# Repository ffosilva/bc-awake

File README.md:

# BC Awake

### ESP32-based smart ATX PSU switch for AMD BC250 with Bluetooth & Wake-on-LAN

The AMD **BC250** is a powerhouse for budget desktop conversions, living room gaming, and local AI workloads — but because it was designed for mining, it lacks an ATX power button and has **no low-power sleep states**, wasting power and generating heat if left idling 24/7.

**BC Awake** solves this by turning an ESP32 into an intelligent power controller for your ATX/SFX PSU (`PS_ON#`). Instead of leaving the system running or fiddling with power cables, BC Awake keeps the machine completely off and brings it up on demand:

- 🎮 **Living Room Console**: Pick up your Bluetooth gamepad (PS4/PS5, Xbox, Switch Pro, 8BitDo) and press the home button — the PC powers on right from your couch.
- ⚡ **On-Demand AI & Game Streaming**: Wake the machine over Wi-Fi via Wake-on-LAN when connecting through Moonlight, Steam Link, or launching intermittent AI model inference and processing workflows.
- 🔘 **Complete Power Management**: Provides a physical power button, automatic PSU shutoff when the OS halts, optional graceful ACPI shutdown, boot watchdog protection, and a captive Wi-Fi portal with OTA firmware updates.

Supports multiple targets from the same repository:
- **ESP32-WROOM (DevKitC)**: Classic Bluetooth (BR/EDR) controller wake.
- **AI-Thinker ESP32-CAM (Bare module)**: Classic Bluetooth wake with onboard flash LED wake indicator.
- **AI-Thinker ESP32-CAM (Carrier Board)**: Dedicated carrier target with BC547/BC548 transistor buffer and ADC2 sensing.
- **ESP32-C3 (SuperMini / DevKitM-1)**: Bluetooth Low Energy (BLE) controller wake.

> [!CAUTION]
> **Hardware Disclaimer**: This project involves custom wiring, ATX power line manipulation, and bare-board hardware. The author is **not responsible** for any BC-250 damages, dead cards, fried components, or any kind of losses or damages resulting from using this firmware, schematics, or documentation. Proceed at your own risk! If deploying the AI-Thinker ESP32-CAM, review the [hardware resilience circuit](docs/pinout.md#ai-thinker-esp32-cam-hardware-resilience-circuit-anti-oscillation) to prevent brownout reboot loops.

## Features

- **Push-button power**: tap to turn on; hold 5 s while running to force off.
- **Follows the board**: if the OS shuts the board down, the PSU is cut automatically.
- **Graceful shutdown** (optional): wire the motherboard's `PWR_BTN#` header to the ESP32 and the button (and a portal "Shut down" action) acts like the real power button — see [Graceful shutdown](#graceful-shutdown-optional).
- **Boot watchdog**: if the board doesn't come up within 10 s, the PSU is released.
- **Bluetooth controller wake** (optional):
  - **Classic Bluetooth (BR/EDR)** on ESP32 / ESP32-CAM (PS4/PS5, Xbox, Switch Pro, 8BitDo in Classic mode).
  - **BLE advertisement wake** on ESP32-C3 (controllers operating in BLE mode).
- **Wake-on-LAN (WOL) over Wi-Fi** (optional): wake the BC250 from Moonlight, Steam Link, or mobile WOL apps targeting your PC's Ethernet MAC address.
- **WiFi setup portal**: configure bound controllers and Wake-on-LAN settings from a phone — no reflashing.
- **Over-the-Air (OTA) firmware updates**: update firmware wirelessly via the setup portal web UI.
- **Firmware versioning**: compile-time semantic versioning and target hardware reporting.

## Wiring

The ESP32 is permanently powered from the ATX connector's **5 V standby** (into the
`5V` / VIN pin), so it runs whether the machine is on or off. Share a common ground
between the ESP, the PSU, and the board.

| ESP32 (DevKitC) | ESP32-CAM | ESP32-C3 | Connects to | Notes |
|-----------------|-----------|----------|-------------|-------|
| GPIO25 | GPIO15 | GPIO5 | Momentary switch, terminal A | Read with internal pull-up |
| GPIO26 | GND (header) | GPIO6 | Momentary switch, terminal B | DevKitC/C3 drives LOW; CAM wires directly to GND |
| GPIO32 | GPIO14 | GPIO4 | ATX `PS_ON#` (green wire) | **Open-drain**, active LOW: LOW = PSU on, released = off |
| GPIO34 | GPIO13 | GPIO3 | BC250 `TPMS1` (pin 9) | ~3.3 V when the board is up, 0 when off (ADC voltage) |
| GPIO27 | GPIO2 | GPIO7 | Motherboard `PWR_BTN#` (optional) | Direct wire; high-Z input, pulled LOW only to emulate a press. See [Graceful shutdown](#graceful-shutdown-optional) |
| 5V / GND | 5V / GND | 5V / GND | PSU standby + common ground | Permanent power for the ESP |

> **`PS_ON#` is 5 V.** It idles at ~5 V (pulled up inside the PSU), above the ESP32's
> GPIO maximum (~3.6 V). Open-drain keeps the ESP from *driving* 5 V, but the pin still
> sees it. A small N-MOSFET/NPN buffer (or at least a ~1 kΩ series resistor) is
> **recommended** — see [docs/pinout.md](docs/pinout.md#ps_on-5-v-caution-recommended-buffer).

`TPMS1` is a higher-impedance signal that hovers near the logic threshold, so it's read
as an analog voltage with hysteresis rather than a digital pin (ADC1 on DevKitC and ESP32-C3; digital input with pull-down on ESP32-CAM).

> [!TIP]
> **ESP32-CAM deployments**: Due to the onboard AMS1117-3.3 regulator's dropout voltage and the 47 kΩ MicroSD pull-up on GPIO13, ESP32-CAM builds are prone to brownout resets and threshold floating. Adding power bulk decoupling (470 µF), an external 4.7 kΩ pull-down on GPIO13, and a BC547/BC548 NPN buffer on GPIO14 is strongly recommended for 24/7 reliability. When using this circuit or the carrier board, flash with `pio run -e esp32cam-carrier -t upload`. See [docs/pinout.md: ESP32-CAM resilience circuit](docs/pinout.md#ai-thinker-esp32-cam-hardware-resilience-circuit-anti-oscillation), the [carrier board guide](docs/esp32cam-carrier-pcb.md), and the dedicated [Bill of Materials](docs/bom.md).

**Full pinout, header diagrams for DevKitC, ESP32-CAM, and ESP32-C3 (SuperMini & DevKitM-1), ATX 24-pin and TPMS1 connector diagrams, the
`PS_ON#` buffer circuit, and the ESP32-CAM resilience circuit: [docs/pinout.md](docs/pinout.md).**

## Button controls

| Action | Result |
|--------|--------|
| Tap while **off** | Power on |
| Hold ≥ 5 s while **on** | Force power off |
| Hold ≥ 8 s while **off** | Enter WiFi setup portal |

The button is the primary control and always works, even with no controller configured.

## Graceful shutdown (optional)

By default the only way the ESP can turn the board off is to cut the PSU (`PS_ON#`), which
is a hard power-off. If you also wire the motherboard's front-panel **`PWR_BTN#`** pin to the
ESP32 (GPIO27 on DevKitC, GPIO2 on ESP32-CAM, GPIO7 on ESP32-C3) and enable the feature in the portal's **Power** tab, the ESP behaves like a real power button:

| Action (feature enabled, machine **on**) | Result |
|------------------------------------------|--------|
| Short press | Mirrored to the board: OS gets an ACPI power-button event and shuts down cleanly |
| Hold the button | Mirrored to the board for as long as you hold it, so the board's own long-press override can apply |
| Hold ≥ 5 s | Unchanged backstop: the PSU is cut immediately |

When the board powers down, `TPMS1` goes low and the existing logic releases `PS_ON#`
automatically. There is no timeout: if the OS hangs, you decide (hold the button 5 s to cut
power). Presses made while the machine is off or booting behave exactly as before. The
`PWR_BTN#` line idles at ~3.4 V on the BC250 board, so it is wired directly and the ESP32
never drives it high. Wiring details: [docs/pinout.md](docs/pinout.md).

## Bluetooth controller wake

This uses **classic Bluetooth (BR/EDR)**, the kind used by most gamepads when paired to
a PC (DualShock 4 / DualSense, Xbox Wireless, 8BitDo, Nintendo Switch Pro Controller / Joy-Con).

A powered-on, paired classic controller doesn't advertise; it *pages* its bonded host.
While the machine is **off**, the ESP32 takes on the BC250's Bluetooth adapter address
and runs **continuous, interlaced page listening**:

1. You turn on the controller (e.g. press the **HOME button** on a Switch controller, or
   power button on an 8BitDo/Xbox/PS controller) → the controller pages its host.
2. The ESP32 catches the page and **rejects** the connection (no link, no authentication,
   so the controller's pairing with the BC250 is never touched) but counts it as
   "controller present", and powers the machine on.
3. Once the machine is powering on, the ESP32 goes silent (stops answering pages). The
   controller's next attempt reaches the real BC250 adapter and connects normally.

When controllers are bound (via the portal), the machine **follows any of your bound controllers**:
turn on any bound controller (up to 8 supported simultaneously) and the machine powers up.
After a power-off there's a short guard window so the controller's reconnect burst can't immediately
switch it back on — turn the controller off within that window to keep the machine down.

Requirements:

- The controller must already be **paired to the BC250**.
- You must give the ESP32 the BC250 Bluetooth **adapter MAC**: on Linux run
  `bluetoothctl show` (the `Controller aa:bb:cc:dd:ee:ff` line); on Windows, Device
  Manager → Bluetooth adapter → Properties → Advanced.

## Wake-on-LAN (Network Wake)

The BC250's onboard Ethernet controller is unpowered when the SFX PSU is off, so it cannot
receive Wake-on-LAN packets natively. When **Enable Wake-on-LAN** is configured:

1. The ESP32 connects to your Wi-Fi network in station (STA) mode and listens for standard
   WOL Magic Packets on UDP ports 9 and 7.
2. When a Magic Packet matching your configured **BC250 Ethernet MAC** arrives from a
   streaming app (Moonlight, Steam Link) or LAN tool, the ESP32 asserts `PS_ON#` to boot the PC.
3. Supports both password-protected and open (passwordless) networks.
4. If disabled, the Wi-Fi radio stays completely off in normal mode for zero RF/power overhead.

## Setup portal

When unconfigured (or after a factory reset), the ESP32 **automatically launches the setup portal** (`BC250_<SUFFIX>`) on initial power-up. While in setup mode, the host machine remains safely powered off and unenergized so you can configure the switch from your smartphone, tablet, or laptop.

If the switch is already configured, hold the power button ≥ 8 s while OFF (or send `'s'` over serial while off) to re-enter setup mode. Hold ≥ 8 s again while in setup mode to return to normal operation.

On every ESP32-CAM build (with or without the carrier board) the onboard red LED (GPIO33) shows the state: off = machine off, fast blink = booting, solid = machine on, 1 Hz blink = setup mode.

### Setup Instructions

1. Connect your smartphone, tablet, or laptop to the open Wi-Fi network **`BC250_<SUFFIX>`** and open `http://192.168.4.1`.
2. Create a portal password (min 6 characters).
3. Access the tabbed interface:
   - **Bluetooth tab**:
     - Enter and save your BC250 Bluetooth adapter MAC (run `bluetoothctl show` on Linux to copy it).
     - Manage controllers: bind paired controllers interactively or add MACs manually (up to 8 controllers).
     - (ESP32-CAM) Toggle flash LED blink on wake.
   - **Network tab**:
     - Configure Wake-on-LAN: check **Enable Wake-on-LAN (Wi-Fi)**, enter your home Wi-Fi SSID, password, device hostname, and BC250 Ethernet MAC address (from `ip link`), then click **Save Network Settings**.
   - **Power tab**:
     - Motherboard power button: toggle optional `PWR_BTN#` mirroring for clean OS shutdown on short press.
   - **System tab**:
     - Firmware update (OTA): upload a compiled `.bin` binary wirelessly.
     - Change portal password or reset configuration back to defaults.
     - Click **Exit setup mode & reboot** to restart the switch into normal operation.

## Build & flash

PlatformIO (pioarduino). Flashing is a single step — the setup portal web UI (`app/index.html`) is automatically gzipped and embedded directly into the firmware binary during the build.

**ESP32-DevKitC (`esp32dev`, default — Classic BT wake):**
```bash
pio run -e esp32dev -t upload
```

**AI-Thinker ESP32-CAM (Bare module — Classic BT wake):**
```bash
pio run -e esp32cam -t upload
```
> *ESP32-CAM flashing note*: Use a USB-to-UART adapter (or ESP32-CAM-MB base board). Connect **GPIO0 to GND** before powering on to enter download mode; disconnect GPIO0 and reset to run.

**AI-Thinker ESP32-CAM (Carrier Board with BC547/BC548 buffer):**
```bash
pio run -e esp32cam-carrier -t upload
```

**ESP32-C3 DevKitM-1 (`esp32-c3-devkitm-1` — BLE wake):**
```bash
pio run -e esp32-c3-devkitm-1 -t upload
```

### Over-the-Air (OTA) Updates

Once the device has been flashed with the dual-bank partition table via USB, all future updates can be applied wirelessly:

1. Compile the firmware binary for your target:
   ```bash
   pio run -e esp32dev   # binary generated at .pio/build/esp32dev/firmware.bin
   ```
2. Hold the switch button ≥ 8 s while OFF to enter the setup portal.
3. Connect to **`BC Awake Setup`** (`http://192.168.4.1`) and unlock.
4. In the **Firmware update (OTA)** card, select your `.bin` file and click **Upload & flash**.
5. The device flashes the inactive bank and automatically reboots into the updated firmware.

> **Note on Initial Partitioning**: The switch uses a dual-bank 1.81 MB OTA layout (`partitions.csv`). Transitioning from older single-partition builds requires **one initial wired flash** (`pio run -t upload`) to repartition flash.

## Notes

- **Multi-target support**: Switching between Classic Bluetooth (ESP32 / ESP32-CAM) and BLE (ESP32-C3) is done by choosing the PlatformIO environment target (`-e esp32dev`, `-e esp32cam`, or `-e esp32-c3-devkitm-1`).
- **WiFi TX power** for the portal's SoftAP is `AP_TX_POWER` in
  [include/board.h](include/board.h) (lowered automatically on ESP32-C3 to prevent the mini RF bug).
- Serial debug runs at **115200** baud.
- Pin assignments and all timing constants live in [include/board.h](include/board.h).

## How to Contribute

Contributions are what make open-source projects thrive! Whether you are an experienced embedded developer or just getting started with ESP32s, your help is welcome and deeply appreciated. Every contribution — from reporting a minor bug to adding support for new hardware — helps make BC Awake better for everyone.

### Ways you can help

- **Report bugs and issues**: Encountered unexpected behavior, boot watchdog resets, or connection issues? [Open an issue](https://github.com/ffosilva/bc-awake/issues) detailing your hardware board, controller model, and serial logs (`115200` baud).
- **Suggest features & improvements**: Have ideas for additional controller modes, new hardware targets, or web portal enhancements? Open a feature request to start a discussion.
- **Submit Pull Requests**: Bug fixes, code optimizations, web UI updates, and documentation improvements are all welcome.
- **Test hardware & controllers**: BC Awake supports various ESP32 boards (DevKitC, ESP32-CAM, ESP32-C3) and countless Bluetooth/BLE controllers. Testing on your hardware and reporting what works helps expand our compatibility list.

### Architectural Decisions & OpenSpec

This project uses [OpenSpec](openspec/) to track architectural decisions, system specifications, and planned changes under the `openspec/` directory.

- **Great to have**: If you're planning a larger architectural change or new subsystem, proposing or documenting it via OpenSpec is a fantastic bonus and helps maintain a clear history of design choices.
- **Not a requirement**: You do **not** need to learn or use OpenSpec to contribute. Feel free to open a regular issue or pull request, and we will happily collaborate with you to help integrate your changes and document any specs needed.

### Getting Started with PRs

1. Fork the repository and clone your fork locally.
2. Create a feature branch (`git checkout -b feature/my-feature`).
3. Make your changes and test the build for relevant targets (e.g., `pio run -e esp32dev`).
4. Commit your changes using clear commit messages.
5. Push to your branch and open a Pull Request with a summary of what you did and why.

## Support

If you find BC Awake useful and would like to support its ongoing development, consider buying me a coffee:

## License

This project is licensed under the GNU General Public License v3.0 - see the [LICENSE](LICENSE) file for details.

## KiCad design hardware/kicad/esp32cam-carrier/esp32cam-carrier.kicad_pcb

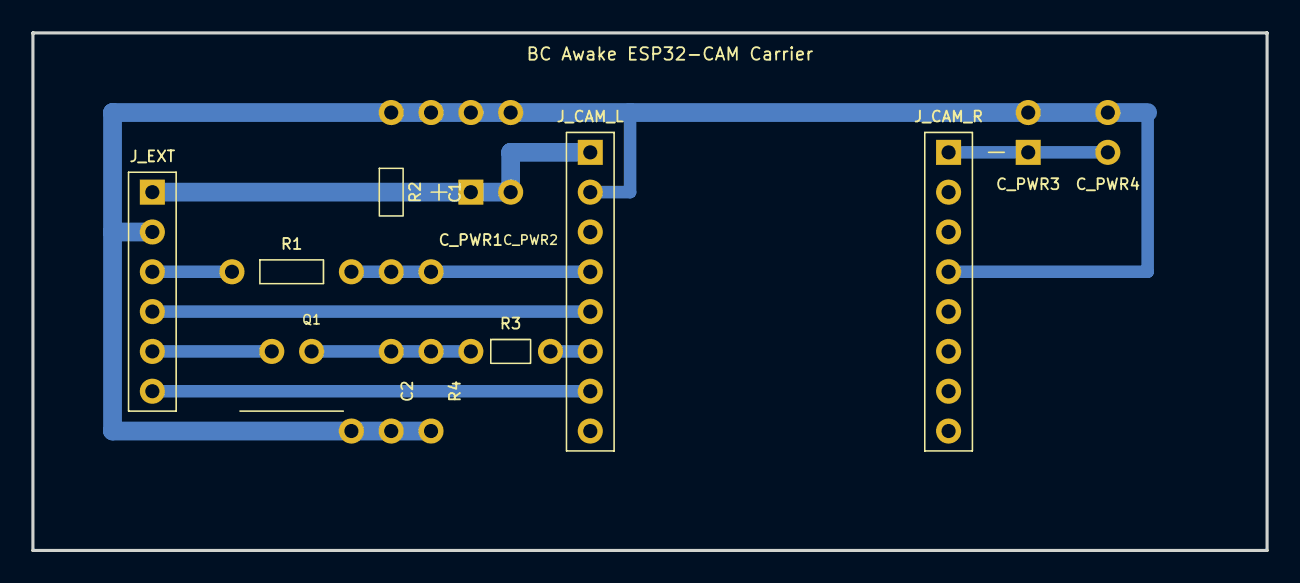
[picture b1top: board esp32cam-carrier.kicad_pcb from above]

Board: 2 copper layers, 78.7 x 33.0 mm, 14 parts (0 on the bottom side), 10 nets.

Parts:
C1, C2: 100nF; C_Disc_D5.0mm_W2.5mm_P2.50mm
C_PWR1: 470uF; CP_Radial_D8.0mm_P3.50mm
C_PWR2, C_PWR4: 100nF; C_Disc_D5.0mm_W2.5mm_P2.50mm
C_PWR3: 47uF; CP_Radial_D6.3mm_P2.50mm
J_CAM_L: ESP32-CAM_L; PinSocket_1x08_P2.54mm_Vertical
J_CAM_R: ESP32-CAM_R; PinSocket_1x08_P2.54mm_Vertical
J_EXT: Ext_Terminals; PinHeader_1x06_P2.54mm_Vertical
Q1: BC547; TO-92_Inline
R1, R3: 1k; R_Axial_DIN0207_L6.3mm_D2.5mm_P7.62mm_Horizontal
R2: 4.7k; R_Axial_DIN0207_L6.3mm_D2.5mm_P7.62mm_Horizontal
R4: 100k; R_Axial_DIN0207_L6.3mm_D2.5mm_P7.62mm_Horizontal

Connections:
+3V3: C_PWR3.1, C_PWR4.1, J_CAM_R.1
+5VSB: C_PWR1.1, C_PWR2.1, J_CAM_L.1, J_EXT.1
BTN_A: J_CAM_L.5, J_EXT.4
GND: C1.1, C2.2, C_PWR1.2, C_PWR2.2, C_PWR3.2, C_PWR4.2, J_CAM_L.2, J_CAM_R.4, J_EXT.2, Q1.3, R2.1, R4.2
NET_GATE: C2.1, Q1.2, R3.1, R4.1
NET_IO13: C1.2, J_CAM_L.4, R1.2, R2.2
NET_IO14: J_CAM_L.6, R3.2
PS_ON#: J_EXT.5, Q1.1
PWR_BTN#: J_CAM_L.7, J_EXT.6
TPMS1: J_EXT.3, R1.1

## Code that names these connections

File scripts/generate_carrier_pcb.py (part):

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    {"lib": "Device:C", "ref": "C_PWR2", "val": "100nF", "fp": "Capacitor_THT:C_Disc_D5.0mm_W2.5mm_P2.50mm", "x": 101.6, "y": 114.3, "rot": 0, "pins": ["1", "2"], "desc": "5V Ceramic Decoupling"},
    {"lib": "Device:C_Polarized", "ref": "C_PWR3", "val": "47uF_16V", "fp": "Capacitor_THT:CP_Radial_D6.3mm_P2.50mm", "x": 203.2, "y": 63.5, "rot": 0, "pins": ["1", "2"], "desc": "3.3V Bulk Decoupling"},
    {"lib": "Device:C", "ref": "C_PWR4", "val": "100nF", "fp": "Capacitor_THT:C_Disc_D5.0mm_W2.5mm_P2.50mm", "x": 215.9, "y": 63.5, "rot": 0, "pins": ["1", "2"], "desc": "3.3V Ceramic Decoupling"},
    {"lib": "Device:R", "ref": "R1", "val": "1k", "fp": "Resistor_THT:R_Axial_DIN0207_L6.3mm_D2.5mm_P7.62mm_Horizontal", "x": 76.2, "y": 38.1, "rot": 90, "pins": ["1", "2"], "desc": "TPMS1 series resistor"},
    {"lib": "Device:R", "ref": "R2", "val": "4.7k", "fp": "Resistor_THT:R_Axial_DIN0207_L6.3mm_D2.5mm_P7.62mm_Horizontal", "x": 88.9, "y": 38.1, "rot": 0, "pins": ["1", "2"], "desc": "TPMS1 pull-down"},
    {"lib": "Device:C", "ref": "C1", "val": "100nF", "fp": "Capacitor_THT:C_Disc_D5.0mm_W2.5mm_P2.50mm", "x": 101.6, "y": 38.1, "rot": 0, "pins": ["1", "2"], "desc": "TPMS1 filter"},
    {"lib": "Transistor_BJT:BC547", "ref": "Q1", "val": "BC547", "fp": "Package_TO_SOT_THT:TO-92_Inline", "x": 63.5, "y": 88.9, "rot": 0, "pins": ["1", "2", "3"], "desc": "PS_ON# NPN Buffer"},
    {"lib": "Device:R", "ref": "R3", "val": "1k", "fp": "Resistor_THT:R_Axial_DIN0207_L6.3mm_D2.5mm_P7.62mm_Horizontal", "x": 88.9, "y": 88.9, "rot": 90, "pins": ["1", "2"], "desc": "BC547 base resistor"},
    {"lib": "Device:R", "ref": "R4", "val": "100k", "fp": "Resistor_THT:R_Axial_DIN0207_L6.3mm_D2.5mm_P7.62mm_Horizontal", "x": 76.2, "y": 101.6, "rot": 0, "pins": ["1", "2"], "desc": "BC547 base pull-down"},
    {"lib": "Device:C", "ref": "C2", "val": "100nF", "fp": "Capacitor_THT:C_Disc_D5.0mm_W2.5mm_P2.50mm", "x": 63.5, "y": 101.6, "rot": 0, "pins": ["1", "2"], "desc": "BC547 base snubber"}
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# 1. J_EXT (1x6 pin header) at Col 2, Rows 3..8
# Pin 1 (Row 3): +5VSB
# Pin 2 (Row 4): GND
# Pin 3 (Row 5): TPMS1
# Pin 4 (Row 6): BTN_A
# Pin 5 (Row 7): PS_ON#
# Pin 6 (Row 8): PWR_BTN#
ext_pads = [
    (1, gx(2), gy(3), 2, "+5VSB", True),
    (2, gx(2), gy(4), 1, "GND", False),
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    (3, gx(13), gy(4), 0, "", False),           # IO12 (NC)
    (4, gx(13), gy(5), 5, "NET_IO13", False),   # IO13 (BOARD_SENSE)
    (5, gx(13), gy(6), 8, "BTN_A", False),      # IO15 (BUTTON_SENSE)
    (6, gx(13), gy(7), 10, "NET_IO14", False),  # IO14 (PS_ON_PIN)
    (7, gx(13), gy(8), 9, "PWR_BTN#", False),   # IO2  (PWR_BTN_PIN)
    (8, gx(13), gy(9), 0, "", False)            # IO4  (Flash LED - NC)
]
cam_l_str = "\n".join([pad_tht(p[0], p[1], p[2], p[3], p[4], p[5]) for p in cam_l_pads])
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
